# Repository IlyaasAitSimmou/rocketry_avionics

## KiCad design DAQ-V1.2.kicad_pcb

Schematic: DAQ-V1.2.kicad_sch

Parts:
C1, C4: 10 µF (0603); C_0603_1608Metric
C3, C8, C11, C13, C15, C35: C (100 nF); C_0603_1608Metric
C5, C7: 2.2 µF; C_0603_1608Metric
C6: C (10 µF); C_0603_1608Metric
C9, C10, C12, C14, C19, C20, C21, C29: 100 nF (0603); C_0603_1608Metric
C16: C (1 µF); C_0603_1608Metric
C17, C22: 1 µF (0603); C_0603_1608Metric
C18, C31: C (0.1 µF); C_0603_1608Metric
C23: 100 µF; C_0603_1608Metric
C24: 1 µF; C_0603_1608Metric
C30: C (200 nF); C_0603_1608Metric
C57, C58, C59, C60: 22 pF (0603); C_0603_1608Metric
C(BME688)2: C (100 nF); C_0603_1608Metric
C(BNO086)1: C (0.1 µF); C_0603_1608Metric
CIN1, CIN2: 10 µF (0805); C_0805_2012Metric
COUT1, COUT2, COUT3: 22 µF (0805); C_0805_2012Metric
CVAUX1: 100 nF; C_0603_1608Metric
D1: LED; LED_0603_1608Metric
FB1: FerriteBead_Small; L_0603_1608Metric
FB2: FerriteBead; L_1008_2520Metric
H1, H2, H3, H4: MountingHole; MountingHole_2.2mm_M2
J2: Conn_02x05_Odd_Even; PinHeader_2x05_P1.27mm_Vertical
J3: Conn_01x02; JST_PH_S2B-PH-K_1x02_P2.00mm_Horizontal
J4: DM3BT-DSF-PEJS; HRS_DM3BT-DSF-PEJS
L1: 1.5 µH; L_1008_2520Metric
LS1: PKLCS1212E2000-R1; SPKR_PKLCS1212E2000-R1; PARTREV January 22, 2018
Power_On_LED1: RED; LED_0603_1608Metric
R1: 470 kΩ; R_0603_1608Metric
R2: 150 kΩ; R_0603_1608Metric
R4: 100 kΩ; R_0603_1608Metric
R5: 10 kΩ; R_0603_1608Metric
R7: R (330 Ω); R_0603_1608Metric
R(ADXL367)1: R (10 kΩ); R_0603_1608Metric
R(NRESET)1: R (10 kΩ); R_0603_1608Metric
R(PULL)1, R(PULL)2, R(PULL)13, R(PULL)14, R(PULL)15, R(PULL)16, R(PULL)18, R(PULL)19: R (4.7 kΩ); R_0603_1608Metric
R(PULL)3, R(PULL)10: R (10 kΩ); R_0603_1608Metric
R(PULL)4: R (100 kΩ); R_0603_1608Metric
R(PULL)9: R (1.5 kΩ); R_0603_1608Metric
R_Pull_MicroSD_1, R_Pull_MicroSD_2, R_Pull_MicroSD_3, R_Pull_MicroSD_4, R_Pull_MicroSD_5, R_Pull_MicroSD_6: 4.7 kΩ; R_0603_1608Metric
R_Series_MicroSD_1, R_Series_MicroSD_2, R_Series_MicroSD_3: 33 Ω; R_0603_1608Metric
U1: STM32H753VITx; LQFP-100_14x14mm_P0.5mm
U2: BNO086; IC_BNO086; PARTREV v1.17
U4: BME688; IC_BME688; PARTREV 1.0
U5: ADXL367BCCZ; CC-12-4_ADI
U6: BMP581; Manufacturer_Part_Number BMP581
U8: TPS63070RNMT; RNM0015A
Y1: ABLS-16.000MHZ-B4-T; XTAL_ABLS-16.000MHZ-B4-T; PARTREV 02.16.2021
Y2: 9HT7-32.768KBZF-T; OSCCC690X140X130-4N

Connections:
+3.3V: C3.2, C4.1, C6.2, C8.2, C9.1, C10.1, C11.2, C12.1, C13.2, C14.1, C15.2, C16.2, C17.1, C19.1, C20.1, C23.1, C24.1, C(BME688)2.2, COUT1.1, COUT2.1, COUT3.1, FB1.2, FB2.1, J2.1, J4.4 (VDD), Power_On_LED1.2 (A), R1.1, R4.1, R(NRESET)1.1, R(PULL)1.1, R(PULL)2.1, R(PULL)3.2, R(PULL)10.2, R(PULL)13.1, R(PULL)14.1, R(PULL)15.1, R(PULL)16.1, R(PULL)18.1, R(PULL)19.1, R_Pull_MicroSD_1.2, R_Pull_MicroSD_2.2, R_Pull_MicroSD_3.2, R_Pull_MicroSD_4.2, R_Pull_MicroSD_5.2, R_Pull_MicroSD_6.1, U1.6 (VBAT), U1.11 (VDD), U1.27 (VDD), U1.50 (VDD), U1.75 (VDD), U1.100 (VDD), U2.3 (VDD), U2.28 (VDDIO), U4.2 (CSB), U4.6 (VDDIO), U4.8 (VDD), U5.3 (MISO/ASEL), U6.1 (VDDIO), U6.6 (CSB), U6.10 (VDD), U8.7 (VOUT), U8.8 (VOUT); also elsewhere on the board
+3.3VA: C21.1, C22.1, FB1.1, U1.21 (VDDA)
/ADXL367 SCL: R(PULL)19.2, U1.67 (PA8), U5.4 (*CS/SCL)
/ADXL367 SDA: R(PULL)18.2, U1.66 (PC9), U5.2 (MOSI/SDA)
/BME688 SCL: R(PULL)13.2, U1.59 (PD12), U4.4 (SCK)
/BME688 SDA: R(PULL)14.2, U1.60 (PD13), U4.3 (SDI)
/BMP581 INT: U1.91 (PB5), U6.7 (INT)
/BMP581 SCL: R(PULL)15.2, U1.46 (PB10), U6.2 (SCK)
/BMP581 SDA: R(PULL)16.2, U1.47 (PB11), U6.4 (SDI)
/BNO086 INT: U1.90 (PB4), U2.14 (~H_INT)
/BNO086 NRESET: R(NRESET)1.2, U1.64 (PC7), U2.11 (~RST)
/BNO086 SCL: R(PULL)1.2, U1.92 (PB6), U2.19 (H_SCL/SCK/RX)
/BNO086 SDA: R(PULL)2.2, U1.93 (PB7), U2.20 (H_SDA/H_MISO/TX)
/BOOT0: R(PULL)4.1, U1.94 (BOOT0)
/NRST: C29.2, J2.10, R(PULL)3.1, U1.14 (NRST)
/PA4: J4.2 (DAT3/CD), R_Pull_MicroSD_3.1, U1.28 (PA4)
/PA5: J4.5 (CLK), R_Series_MicroSD_1.1
/PA6: J4.7 (DAT0), R_Pull_MicroSD_1.1, R_Series_MicroSD_2.1
/PA7: J4.3 (CMD), R_Pull_MicroSD_2.1, R_Series_MicroSD_3.1
/PE2: J4.SW-A, R_Pull_MicroSD_6.2, U1.1 (PE2)
/PWR_LED_K: Power_On_LED1.1 (K), R(PULL)9.2
/SWCLK: J2.4, U1.76 (PA14)
/SWDIO: J2.2, U1.72 (PA13)
/SWO: J2.6, U1.89 (PB3)
/VDD: C1.1, CIN1.1, CIN2.1, J3.2, R5.1, U8.12 (VIN), U8.13 (VIN)
GND: C1.2, C3.1, C4.2, C5.1, C6.1, C7.1, C8.1, C9.2, C10.2, C11.1, C12.2, C13.1, C14.2, C15.1, C16.1, C17.2, C18.1, C19.2, C20.2, C21.2, C22.2, C23.2, C24.2, C29.1, C30.1, C31.1, C35.2, C57.1, C58.1, C59.1, C60.1, C(BME688)2.1, C(BNO086)1.1, CIN1.2, CIN2.2, COUT1.2, COUT2.2, COUT3.2, CVAUX1.2, D1.1 (K), J2.3, J2.5, J2.9, J3.1, J4.6 (VSS), J4.S1 (SHIELD), J4.S2 (SHIELD), J4.S3 (SHIELD), J4.S4 (SHIELD), J4.SW-B, LS1.N, R2.2, R(PULL)4.2, R(PULL)9.1, U1.10 (VSS), U1.19 (VSSA), U1.26 (VSS), U1.49 (VSS), U1.74 (VSS), U1.99 (VSS), U2.2 (GND), U2.5 (PS1), U2.6 (PS0/WAKE), U2.17 (SA0/H_MOSI), U2.25 (GNDIO), U4.1 (GND), U4.5 (SDO), U4.7 (GND), U5.7 (GND), U5.11 (GND), U6.3 (VSS_1), U6.5 (SDO), U6.8 (VSS_2), U6.9 (VSS_3), U8.1 (PS_SYNC), U8.4 (GND), U8.6 (FB2), U8.10 (PGND), U8.15 (VSEL); also elsewhere on the board
unnamed: C5.2, U1.48 (VCAP)
unnamed: C7.2, U1.73 (VCAP)
unnamed: D1.2 (A), R7.2
unnamed: J4.8 (DAT1), R_Pull_MicroSD_5.1
unnamed: J4.1 (DAT2), R_Pull_MicroSD_4.1
unnamed: R_Series_MicroSD_1.2, U1.29 (PA5)
unnamed: R_Series_MicroSD_2.2, U1.30 (PA6)
unnamed: R_Series_MicroSD_3.2, U1.31 (PA7)
unnamed: LS1.P, U1.4 (PE5)
unnamed: R7.1, U1.38 (PE8)
unnamed: C57.2, U1.12 (PH0), Y1.2
unnamed: C58.2, U1.13 (PH1), Y1.1
unnamed: C35.1, U1.20 (VREF+)
unnamed: C(BNO086)1.2, U2.9 (CAP)
unnamed: C60.2, U2.27 (XIN32), Y2.4
unnamed: C59.2, U2.26 (XOUT32/CLKSEL1), Y2.1
unnamed: R(PULL)10.1, U2.4 (~BOOT)
unnamed: C31.2, FB2.2, R(ADXL367)1.1, U5.12 (VDDIO)
unnamed: C30.2, U5.9 (VREG_OUT)
unnamed: C18.2, R(ADXL367)1.2, U5.10 (VS)
unnamed: R5.2, U8.14 (EN)
unnamed: R1.2, R2.1, U8.5 (FB)
unnamed: L1.1, U8.11 (L1)
unnamed: L1.2, U8.9 (L2)
unnamed: R4.2, U8.2 (PG)
unnamed: CVAUX1.1, U8.3 (VAUX)

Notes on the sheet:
GND
5V Regulated Line

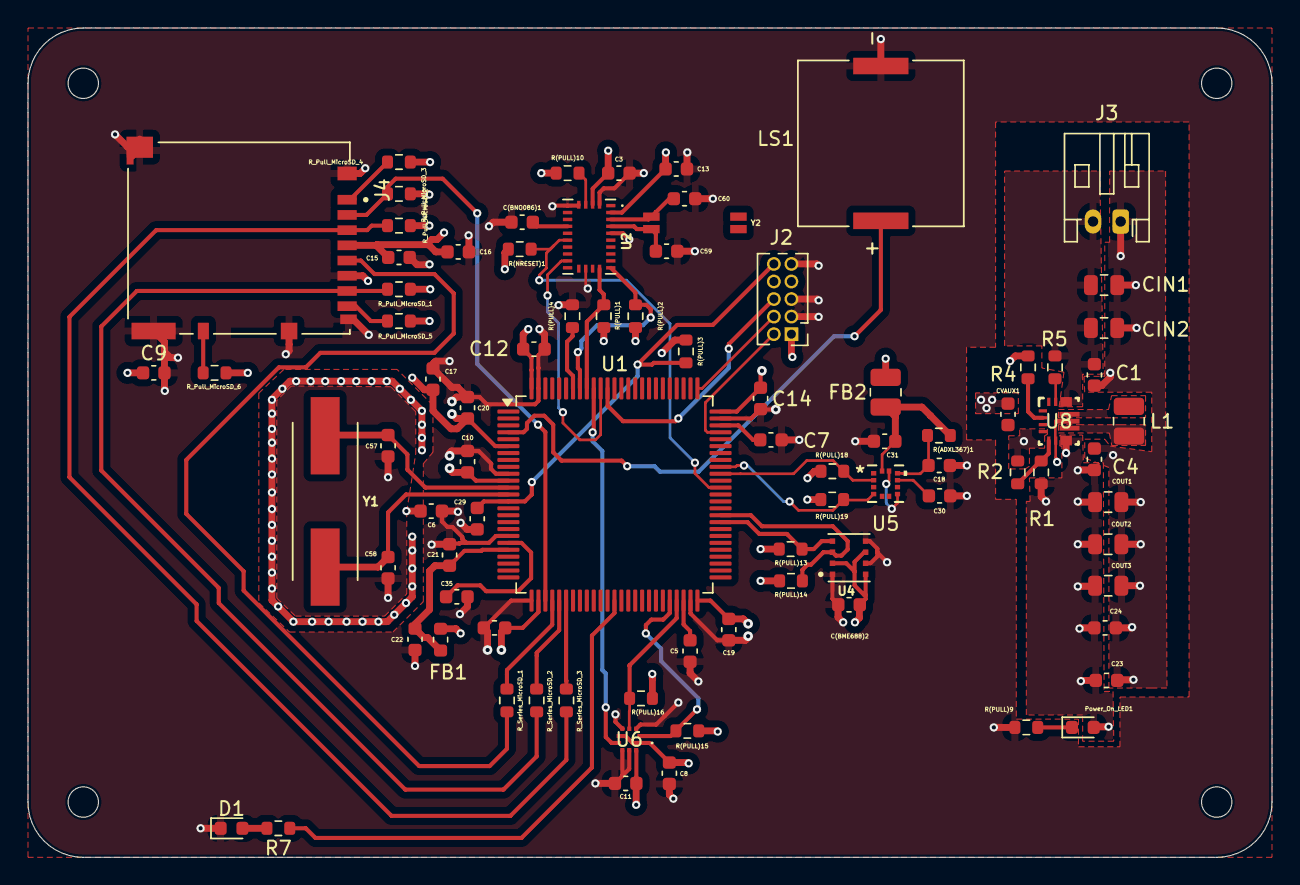
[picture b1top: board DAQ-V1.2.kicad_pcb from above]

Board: 4 copper layers, 90.0 x 60.0 mm, 89 parts (0 on the bottom side), 52 nets.

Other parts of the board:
C9#2: 100 nF (0603); C_0603_1608Metric

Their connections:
+3.3V: C9#2.1; also elsewhere on the board
GND: C9#2.2; also elsewhere on the board

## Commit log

2026-02-05 Flight computer schematic polished and PCB commenced
2026-03-08 Completed DAQ Board (Version 1)
2026-04-01 V2 version || some previous mistakes fixed
